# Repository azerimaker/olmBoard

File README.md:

# olmBoard v0.1
This is a TPS62840 based, ultra-low quiescent current, highly-efficient, breadboard-friendly buck converter module w/:
- Selectable outputs (1.8-3.3 V)
- 60nA Iq, 150nA @ 100% mode
- 20nA shutdown current 
- 750mA max output current

Inital sweep load test results w/ 0.1A and 10 sec increments using EBD-USB load tester. The module works well up to 1A loads (short term), recommended max output current is 750mA. Voltage drop in the graph is due to the USB cable drop, actual voltage is stable around 3.3V up to 1A loads.

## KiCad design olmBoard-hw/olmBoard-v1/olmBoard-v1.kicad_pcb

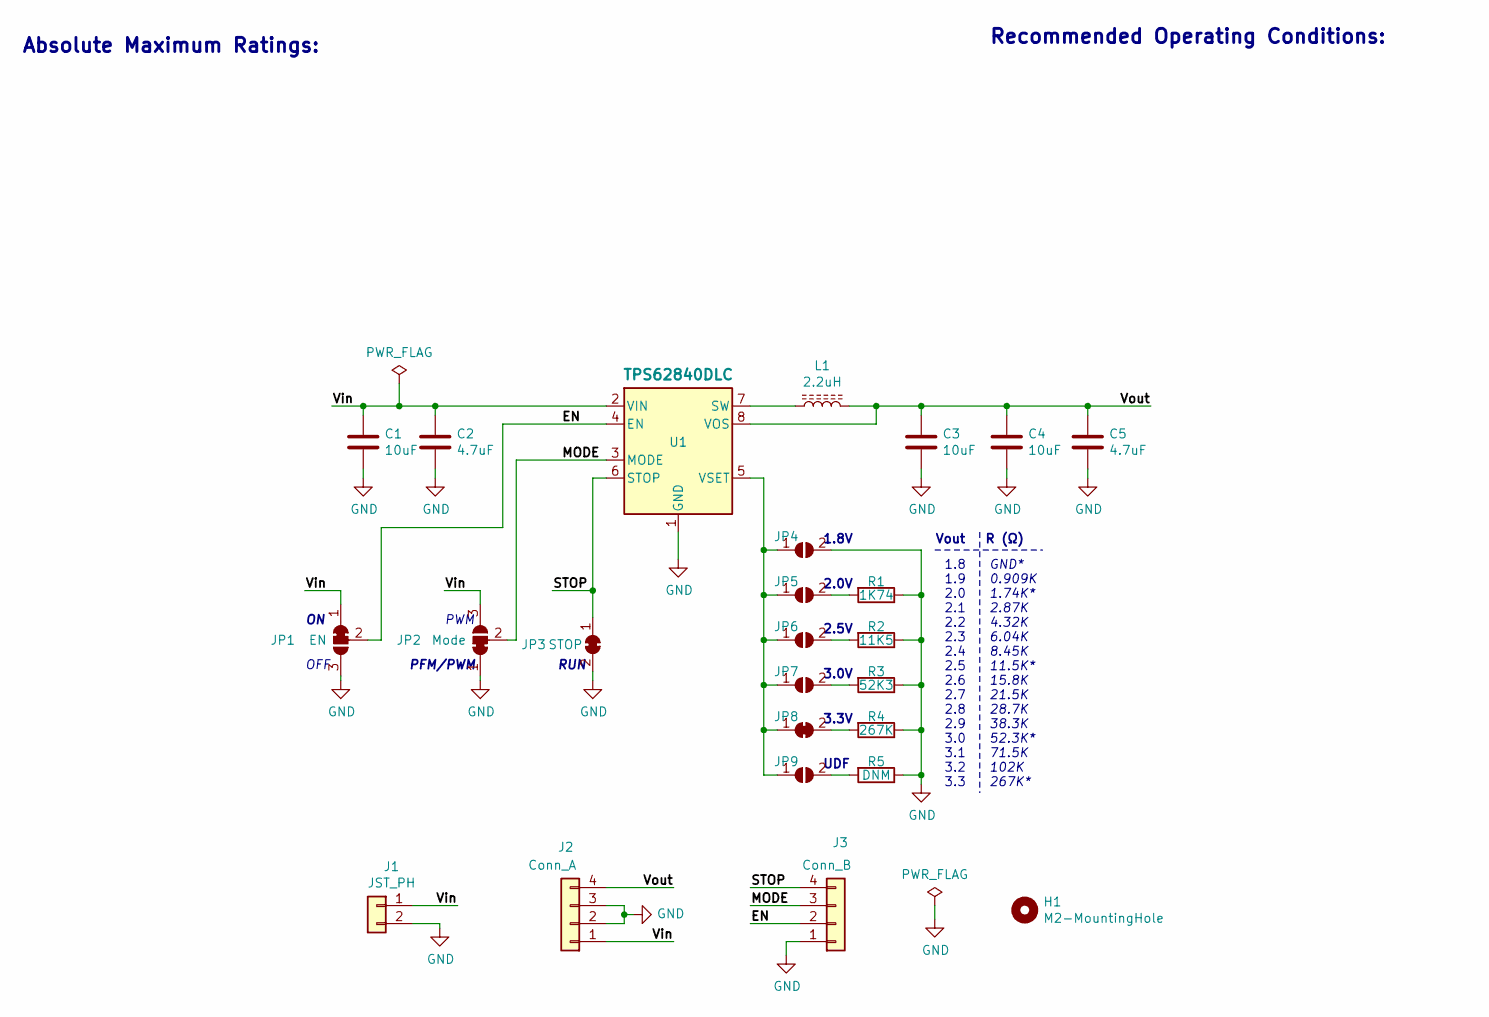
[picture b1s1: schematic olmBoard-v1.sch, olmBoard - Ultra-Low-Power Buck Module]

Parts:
C1, C3, C4: 10uF; C_0603_1608Metric; MPN CL10A106MO8NQNC
C2, C5: 4.7uF; C_0603_1608Metric; MPN GRM188B31A475KE15D
H1: M2-MountingHole; MountingHole_2.2mm_M2_DIN965_Pad
J1: JST_PH; JST_PH_S2B-PH-SM4-TB_1x02-1MP_P2.00mm_Horizontal
J2: Conn_A; PinHeader_1x04_P2.54mm_Vertical
J3: Conn_B; PinHeader_1x04_P2.54mm_Vertical
JP1: EN; SolderJumper-3_P1.3mm_Bridged12_RoundedPad1.0x1.5mm_NumberL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
JP2: Mode; SolderJumper-3_P1.3mm_Bridged12_RoundedPad1.0x1.5mm_NumberL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
JP3: STOP; SolderJumper-2_P1.3mm_Bridged_RoundedPad1.0x1.5mm
JP4, JP5, JP6, JP7, JP8, JP9: Rset; SolderJumper-2_P1.3mm_Open_TrianglePad1.0x1.5mm
L1: 2.2uH; L_0806; MPN TFM201610GHM-2R2MTAA
R1: 1K74; R_0603_1608Metric; MPN 0603WAF1741T5E
R2: 11K5; R_0603_1608Metric; MPN RC0603FR-0711K5L
R3: 52K3; R_0603_1608Metric; MPN RC0603FR-0752K3L
R4: 267K; R_0603_1608Metric; MPN ERJ3EKF2673V
R5: DNM; R_0603_1608Metric
U1: TPS62840DLC; SON-8-1.5x2mm_P0.5mm

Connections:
/EN: J3.2, JP1.2 (C), U1.4 (EN)
/MODE: J3.3, JP2.2 (C), U1.3 (MODE)
/STOP: J3.4, JP3.1 (A), U1.6 (STOP)
/Vin: C1.1, C2.1, J1.1, J2.1, JP1.1 (A), JP2.3 (B), U1.2 (VIN)
/Vout: C3.1, C4.1, C5.1, J2.4, L1.2, U1.8 (VOS)
GND: C1.2, C2.2, C3.2, C4.2, C5.2, J1.2, J2.2, J2.3, J3.1, JP1.3 (B), JP2.1 (A), JP3.2 (B), JP4.2 (B), R1.1, R2.1, R3.1, R4.1, R5.1, U1.1 (GND)
unnamed: JP4.1 (A), JP5.1 (A), JP6.1 (A), JP7.1 (A), JP8.1 (A), JP9.1 (A), U1.5 (VSET)
unnamed: JP5.2 (B), R1.2
unnamed: JP6.2 (B), R2.2
unnamed: JP7.2 (B), R3.2
unnamed: JP8.2 (B), R4.2
unnamed: JP9.2 (B), R5.2
unnamed: L1.1, U1.7 (SW)

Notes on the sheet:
1.8 1.9 2.0 2.1 2.2 2.3 2.4 2.5 2.6 2.7 2.8 2.9 3.0 3.1 3.2 3.3
1.8V
2.0V
2.5V
3.0V
3.3V
UDF
Vout R (Ω)
GND* 0.909K 1.74K* 2.87K 4.32K 6.04K 8.45K 11.5K* 15.8K 21.5K 28.7K 38.3K 52.3K* 71.5K 102K 267K*
PFM/PWM
PWM
OFF
RUN
Absolute Maximum Ratings:
Recommended Operating Conditions:

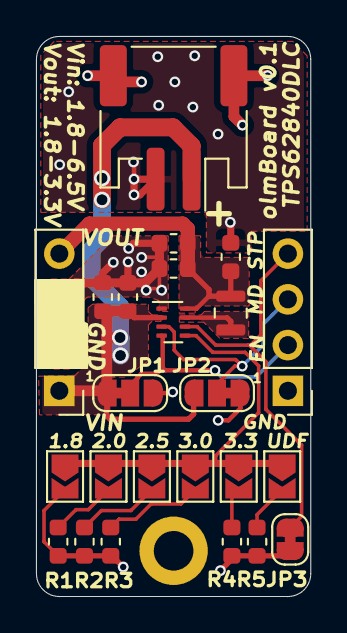
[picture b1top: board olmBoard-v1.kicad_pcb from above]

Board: 2 copper layers, 15.2 x 31.1 mm, 25 parts (0 on the bottom side), 13 nets.

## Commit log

2019-12-03 Design files added
    Version v0.1
2019-12-03 BOM update
2019-12-04 Test results added
2019-12-04 Graphs added
2019-12-04 Readme updates
